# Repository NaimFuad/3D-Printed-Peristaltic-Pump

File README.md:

# 3D-Printed-Peristaltic-Pump
3D printed peristaltic pump intended for precise dosing of liquid

[Video on how it work](https://youtu.be/wXhuivK0bVU)

Status - Work In Progress

The main idea of this project is to allow user to 3D print their own peristaltic pump. The pump able to micro dose liquid and the design allows it to self prime and avoid from bleeding.

An extension of this project can be applied to agricultural field where precise chemical might need to be introduce to plant from time to time.

## Hardware

* Frame - 3D Printed
* 608ZZ Bearing
* M3 Screw
* M3 Treaded Insert

## Electronics
* NEMA 17 Stepper Motor
* PCB - Fabricated from JLCPCB - footprint selected to allow user to hand solder
* A4988 Stepper Motor Driver
* etc. Refer to Bill of Material provided

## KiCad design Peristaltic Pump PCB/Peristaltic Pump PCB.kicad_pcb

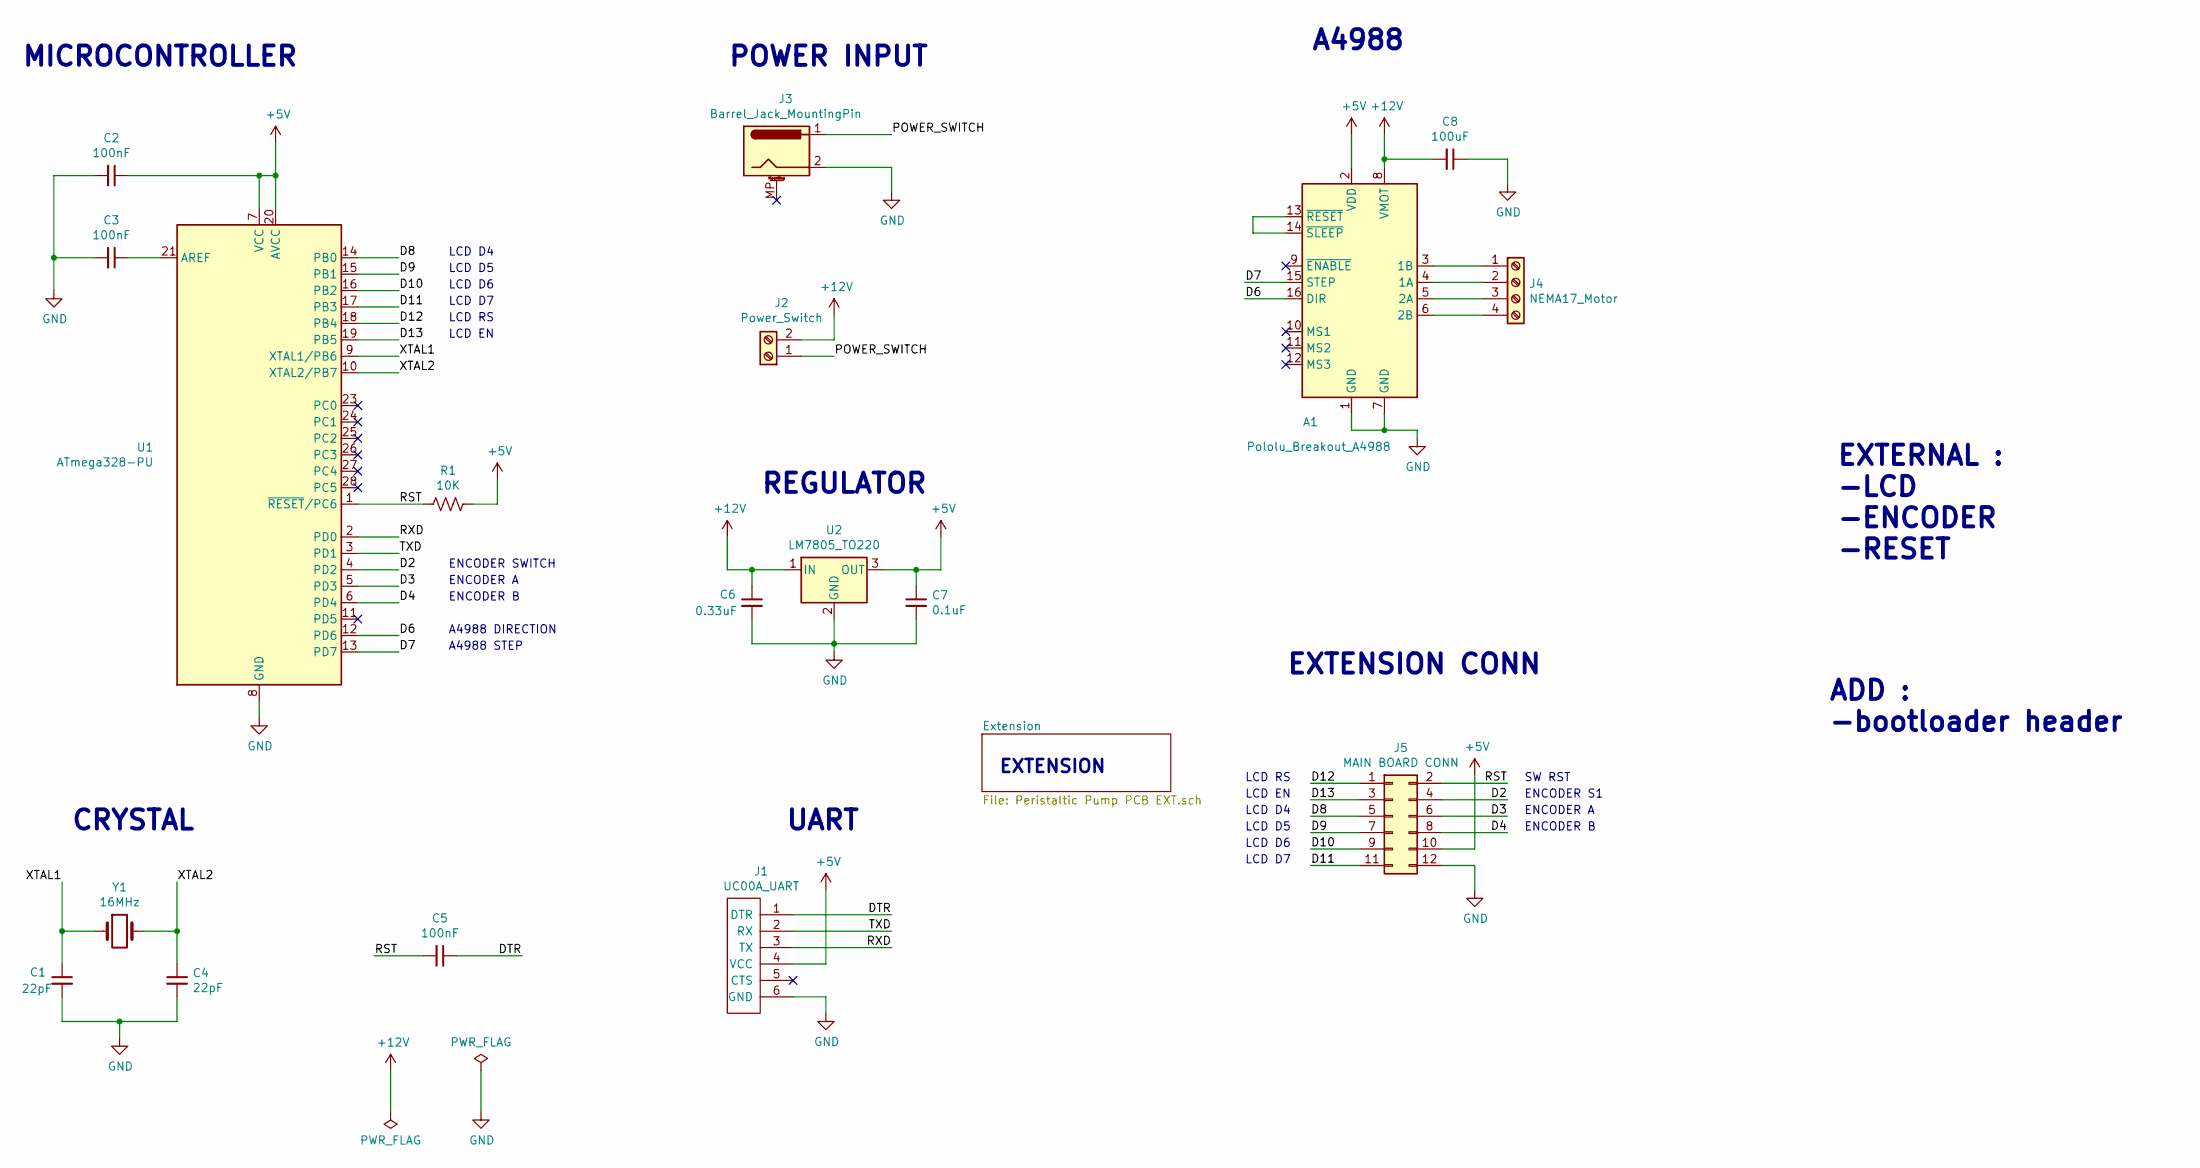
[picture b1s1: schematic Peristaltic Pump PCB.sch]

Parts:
A1: Pololu_Breakout_A4988; Pololu_Breakout-16_15.2x20.3mm
C1, C4: 22pF; C_1206_3216Metric_Pad1.42x1.75mm_HandSolder
C2, C3, C5: 100nF; C_1206_3216Metric_Pad1.42x1.75mm_HandSolder
C6: 0.33uF; CP_Elec_4x5.4
C7: 0.1uF; CP_Elec_4x5.4
C8: 100uF; CP_Elec_6.3x5.8
J1: UC00A_UART; Pin_Header_Straight_1x06_Pitch2.54mm
J2: Power_Switch; Molex_KK-254_AE-6410-02A_1x02_P2.54mm_Vertical
J3: Barrel_Jack_MountingPin; BarrelJack_Horizontal
J4: NEMA17_Motor; Molex_KK-254_AE-6410-04A_1x04_P2.54mm_Vertical
J5: MAIN BOARD CONN; IDC-Header_2x06_P2.54mm_Vertical
R1: 10K; R_1206_3216Metric_Pad1.42x1.75mm_HandSolder
U1: ATmega328-PU; DIP-28_W7.62mm
U2: LM7805_TO220; TO-220-3_Vertical
Y1: 16MHz; Crystal_HC49-4H_Vertical

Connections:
+5V: A1.2 (VDD), C2.1, C7.1, J1.4 (VCC), J5.10, R1.1, U1.7 (VCC), U1.20 (AVCC), U2.3 (OUT)
+12V: A1.8 (VMOT), C6.1, C8.2, J2.2, U2.1 (IN)
/D2: J5.4, U1.4 (PD2)
/D3: J5.6, U1.5 (PD3)
/D4: J5.8, U1.6 (PD4)
/D6: A1.16 (DIR), U1.12 (PD6)
/D7: A1.15 (STEP), U1.13 (PD7)
/D8: J5.5, U1.14 (PB0)
/D9: J5.7, U1.15 (PB1)
/D10: J5.9, U1.16 (PB2)
/D11: J5.11, U1.17 (PB3)
/D12: J5.1, U1.18 (PB4)
/D13: J5.3, U1.19 (PB5)
/DTR: C5.1, J1.1 (DTR)
/POWER_SWITCH: J2.1, J3.1
/RST: C5.2, J5.2, R1.2, U1.1 (~RESET~/PC6)
/RXD: J1.3 (TX), U1.2 (PD0)
/TXD: J1.2 (RX), U1.3 (PD1)
/XTAL1: C1.1, U1.9 (XTAL1/PB6), Y1.1
/XTAL2: C4.1, U1.10 (XTAL2/PB7), Y1.2
GND: A1.1 (GND), A1.7 (GND), C1.2, C2.2, C3.2, C4.2, C6.2, C7.2, C8.1, J1.6 (GND), J3.2, J5.12, U1.8 (GND), U1.22 (GND), U2.2 (GND)
unnamed: A1.3 (1B), J4.1
unnamed: A1.4 (1A), J4.2
unnamed: A1.5 (2A), J4.3
unnamed: A1.6 (2B), J4.4
unnamed: A1.13 (~RESET), A1.14 (~SLEEP)
unnamed: C3.1, U1.21 (AREF)

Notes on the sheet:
UART
POWER INPUT
CRYSTAL
REGULATOR
A4988 STEP
A4988 DIRECTION
ENCODER A
ENCODER B
ENCODER SWITCH
A4988
EXTERNAL : -LCD -ENCODER -RESET
LCD RS
LCD EN
LCD D7
LCD D6
LCD D5
LCD D4
MICROCONTROLLER
EXTENSION CONN
SW RST
ENCODER S1
EXTENSION
ADD : -bootloader header

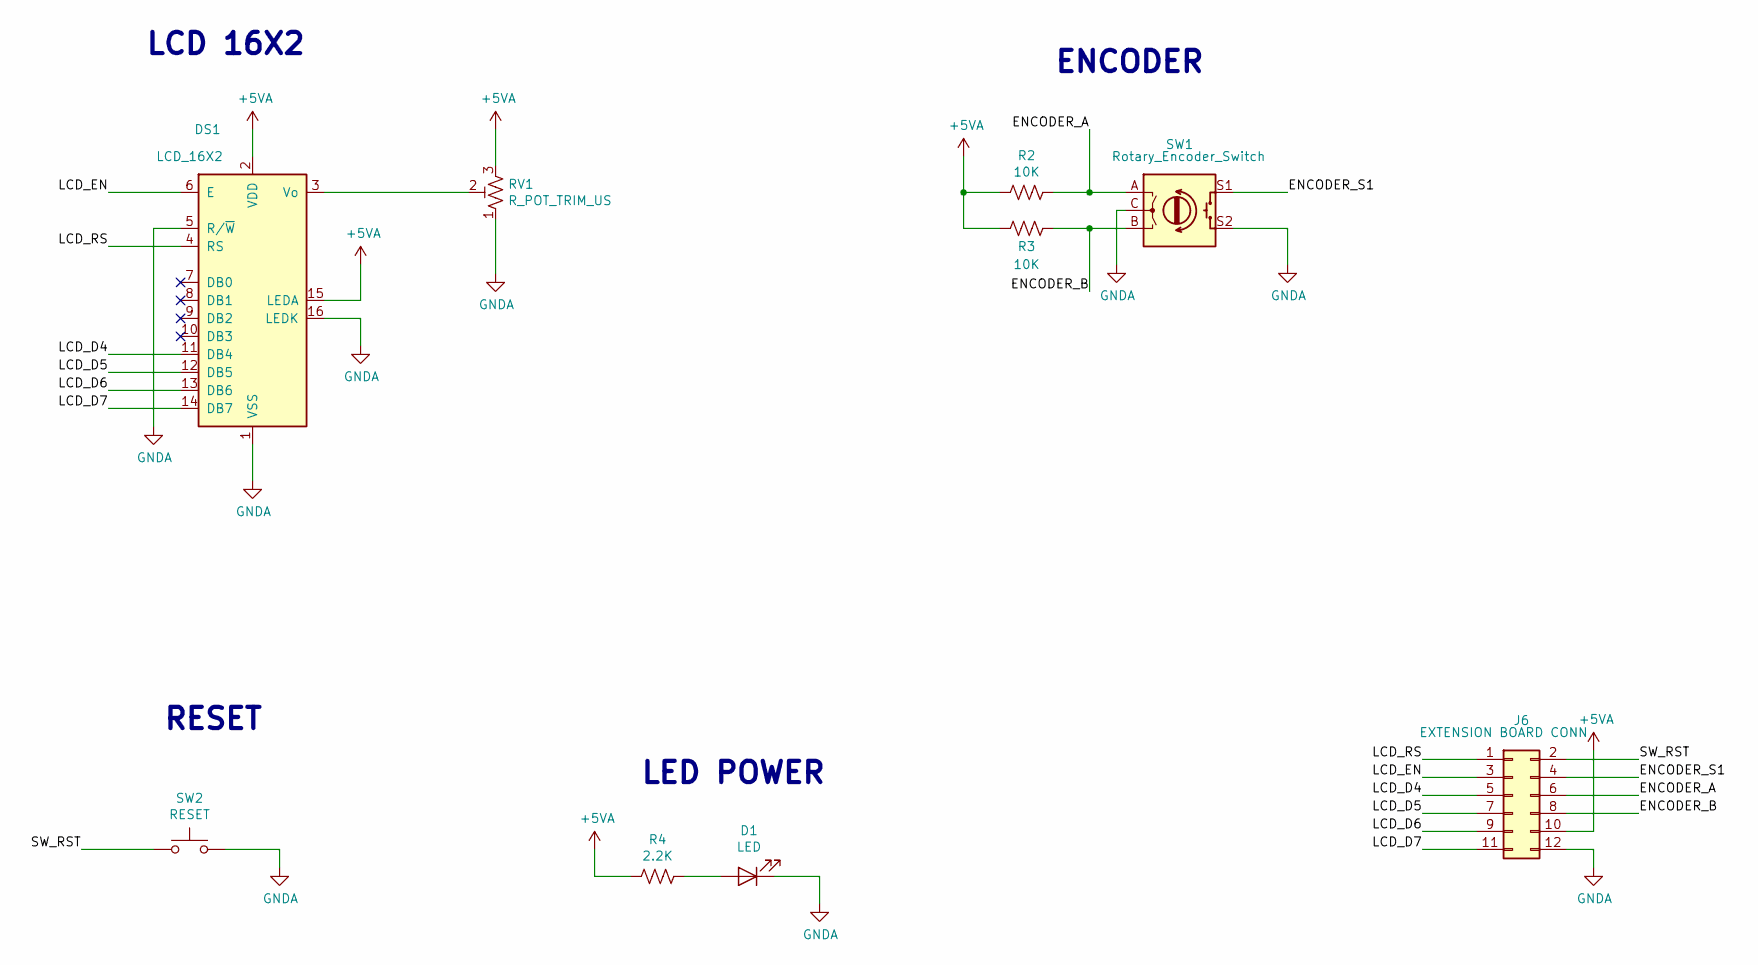
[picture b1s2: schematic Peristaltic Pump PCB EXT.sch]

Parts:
D1: LED; LED_1206_3216Metric_Pad1.42x1.75mm_HandSolder
DS1: LCD_16X2; WC1602A
J6: EXTENSION BOARD CONN; IDC-Header_2x06_P2.54mm_Vertical
R2, R3: 10K; R_1206_3216Metric_Pad1.42x1.75mm_HandSolder
R4: 2.2K; R_1206_3216Metric_Pad1.42x1.75mm_HandSolder
RV1: R_POT_TRIM_US; Potentiometer_Vishay_T73YP_Vertical
SW1: Rotary_Encoder_Switch; RotaryEncoder_Alps_EC11E-Switch_Vertical_H20mm_CircularMoun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
SW2: RESET; SW_PUSH_6mm

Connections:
+5VA: DS1.2 (VDD), DS1.15 (LEDA), J6.10, R2.2, R3.2, R4.2, RV1.3
/Extension/ENCODER_A: J6.6, R2.1, SW1.A
/Extension/ENCODER_B: J6.8, R3.1, SW1.B
/Extension/ENCODER_S1: J6.4, SW1.S1
/Extension/LCD_D4: DS1.11 (DB4), J6.5
/Extension/LCD_D5: DS1.12 (DB5), J6.7
/Extension/LCD_D6: DS1.13 (DB6), J6.9
/Extension/LCD_D7: DS1.14 (DB7), J6.11
/Extension/LCD_EN: DS1.6 (E), J6.3
/Extension/LCD_RS: DS1.4 (RS), J6.1
/Extension/SW_RST: J6.2, SW2.1
GNDA: D1.1 (K), DS1.1 (VSS), DS1.5 (R/~W), DS1.16 (LEDK), J6.12, RV1.1, SW1.C, SW1.S2, SW2.2
unnamed: D1.2 (A), R4.1
unnamed: DS1.3 (Vo), RV1.2

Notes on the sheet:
LCD 16X2
RESET
ENCODER
LED POWER

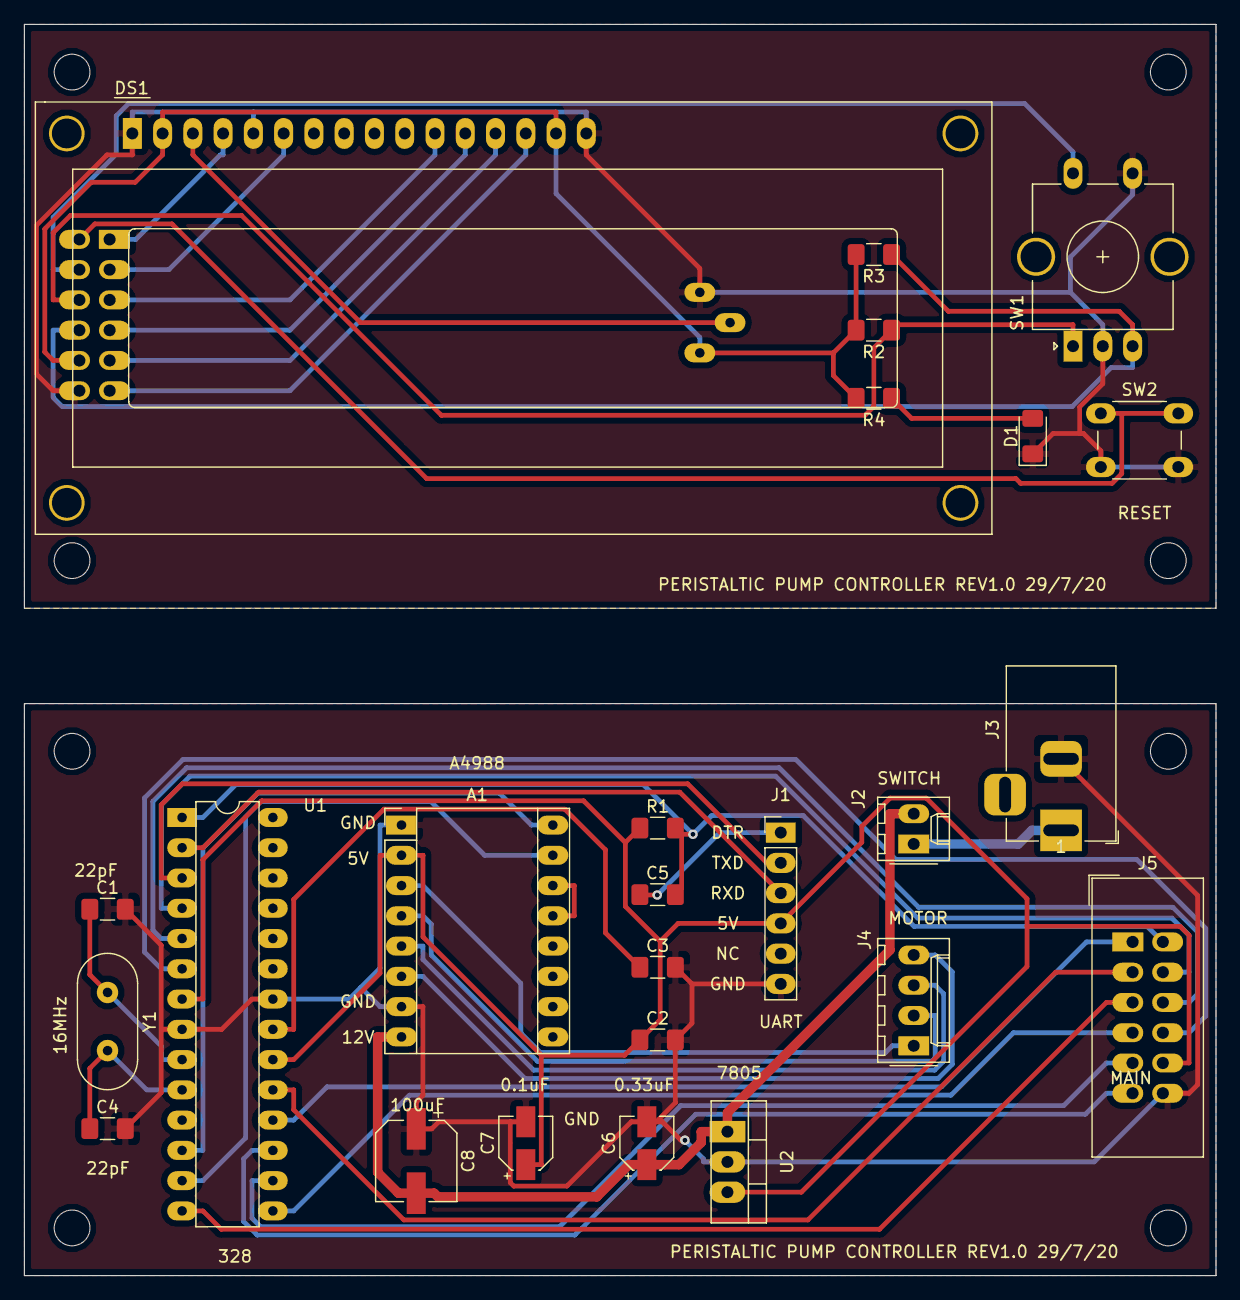
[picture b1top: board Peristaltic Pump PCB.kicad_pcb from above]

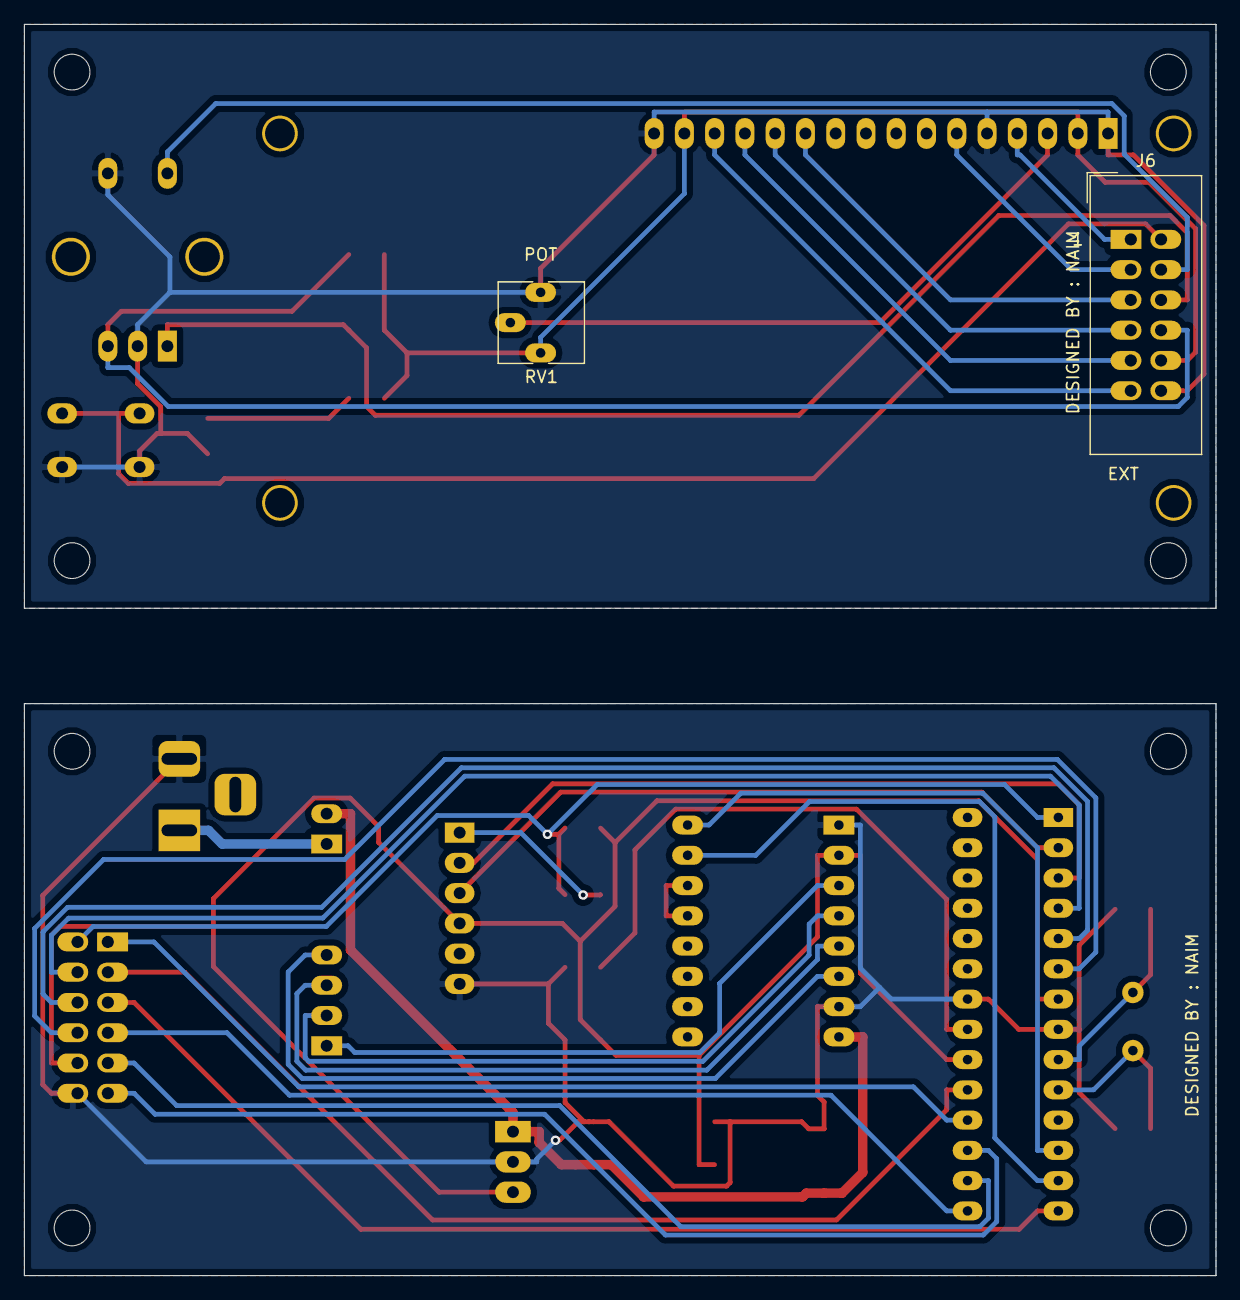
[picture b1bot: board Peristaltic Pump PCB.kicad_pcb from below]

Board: 2 copper layers, 100.0 x 105.0 mm, 35 parts (2 on the bottom side), 41 nets.

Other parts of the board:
MT1, MT2, MT3, MT4, MT5, MT6, MT7, MT8: MountingHole_3mm
